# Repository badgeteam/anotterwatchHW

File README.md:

# AnOtter_Watch

ESP32 driven smart watch with 14-Bit, 2 MSPS Dual Channel scope and component tester.

[Schematics](/schematics_V1.1/anotterwatch.pdf) read more on the [Wiki](https://wiki.badge.team/AnOtter_Watch)

Designed in KiCad

## Current project status

Prototype d0a3733 ordered

[Gerber files](/gerber_V1.0.zip)

## V1.1

# Errors

 - [ ] ESP-Pico-D4 foorpint
 - [ ] Display cutout
 - [ ] TCA9535 GND level is ~0.5V when USB is unplugged
 - [ ] WS2812 leds are not working when USB is plugged
 - [ ] Button down can only be pressed when the battery is connected
 
# Tested
  
  - PMIC
  - Charging
  - WS2812
  - Display
  - I2C switch
  - USB-Plug
  - CH341C
  - Button

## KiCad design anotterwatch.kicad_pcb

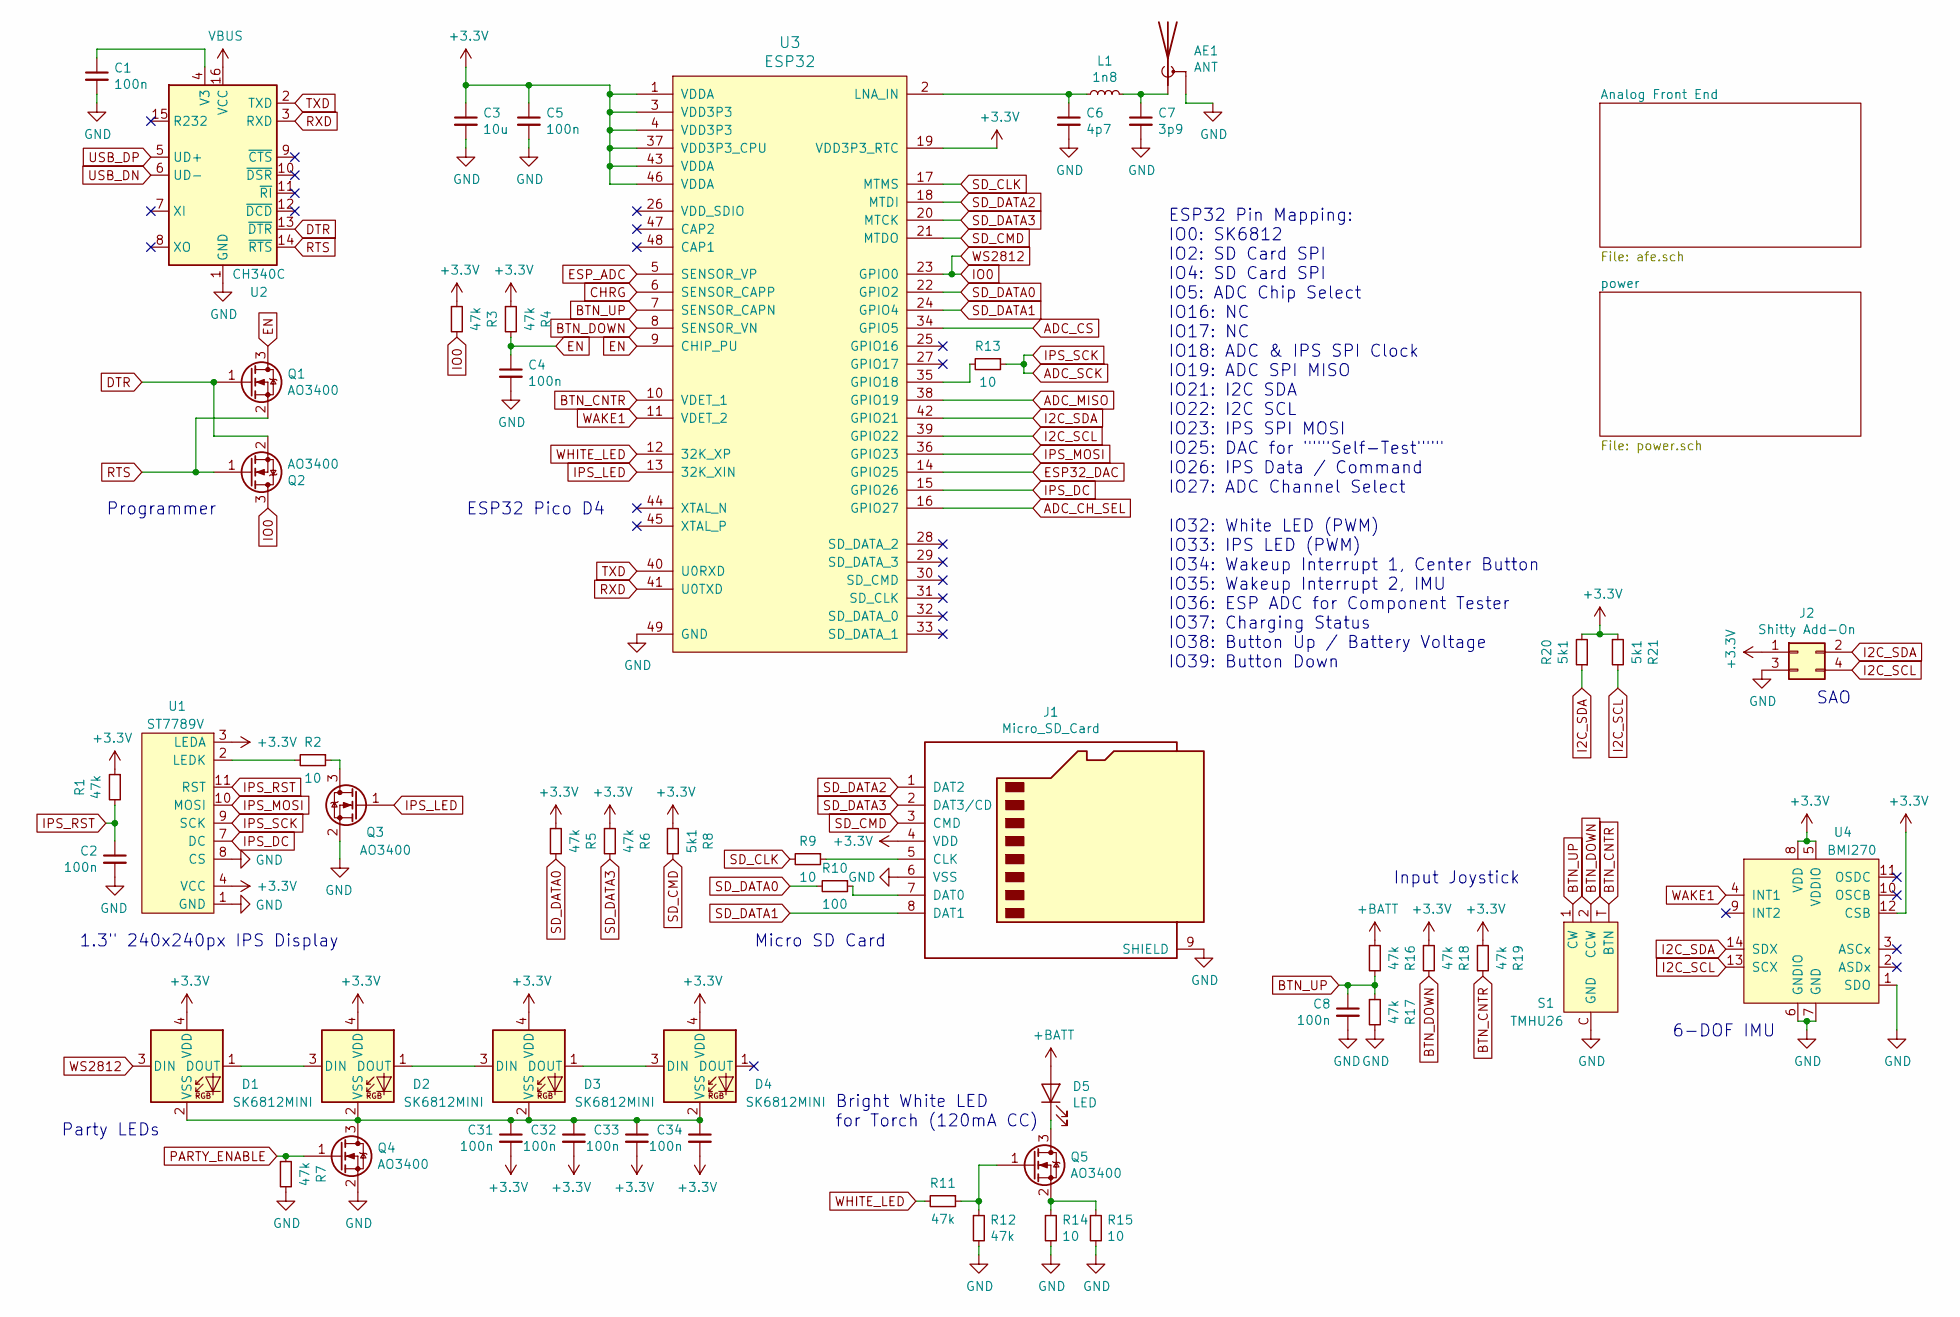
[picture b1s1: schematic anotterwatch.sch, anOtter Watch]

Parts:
AE1: ANT; Texas_SWRA117D_2.4GHz_Left
C1, C2, C4, C5, C8, C31, C32, C33, C34: 100n; C_0402_1005Metric
C3: 10u; C_0603_1608Metric
C6: 4p7; C_0402_1005Metric
C7: 3p9; C_0402_1005Metric
D1, D2, D3, D4: SK6812MINI; LED_SK6812MINI_PLCC4_3.5x3.5mm_P1.75mm
D5: LED; RZX-S020CCW-0.4T
J1: Micro_SD_Card; SUNTECH_ST-TF-003A
J2: Shitty Add-On; PinSocket_2x02_P2.54mm_Vertical_SMD
L1: 1n8; L_0603_1608Metric
Q1, Q2, Q3, Q4, Q5: AO3400; SOT-23
R1, R3, R4, R5, R6, R7, R11, R12, R16, R17, R18, R19: 47k; R_0402_1005Metric
R2, R9, R13, R14, R15: 10; R_0603_1608Metric
R8, R20, R21: 5k1; R_0402_1005Metric
R10: 100; R_0402_1005Metric
S1: TMHU26
U1: ST7789V
U2: CH340C; SOIC-16_3.9x9.9mm_P1.27mm
U3: ESP32; QFN-48-1EP_7x7mm_P0.5mm_EP5.3x5.3mm
U4: BMI270

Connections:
+3V3: C3.1, C5.1, C31.2, C32.2, C33.2, C34.2, D1.4 (VDD), D2.4 (VDD), D3.4 (VDD), D4.4 (VDD), J1.4 (VDD), J2.1, R1.1, R3.1, R4.1, R5.1, R6.1, R8.1, R18.1, R19.1, R20.2, R21.1, U1.3 (LEDA), U1.4 (VCC), U3.1 (VDDA), U3.3 (VDD3P3), U3.4 (VDD3P3), U3.19 (VDD3P3_RTC), U3.37 (VDD3P3_CPU), U3.43 (VDDA), U3.46 (VDDA), U4.5 (VDDIO), U4.8 (VDD), U4.12 (CSB); also elsewhere on the board
ADC_CH_SEL: U3.16 (GPIO27); also elsewhere on the board
ADC_CS: U3.34 (GPIO5); also elsewhere on the board
ADC_MISO: U3.38 (GPIO19); also elsewhere on the board
ADC_SCK: R13.1, U1.9 (SCK); also elsewhere on the board
BTN_CNTR: R19.2, S1.T (BTN), U3.10 (VDET_1)
BTN_DOWN: R18.2, S1.2 (CCW), U3.8 (SENSOR_VN)
BTN_UP: C8.1, R16.2, R17.1, S1.1 (CW), U3.7 (SENSOR_CAPN)
CHRG: U3.6 (SENSOR_CAPP); also elsewhere on the board
DTR: Q1.1 (G), Q2.2 (S), U2.13 (~DTR)
EN: C4.1, Q1.3 (D), R4.2, U3.9 (CHIP_PU)
ESP32_DAC: U3.14 (GPIO25); also elsewhere on the board
ESP_ADC: U3.5 (SENSOR_VP); also elsewhere on the board
GND: AE1.2 (Shield), C1.2, C2.2, C3.2, C4.2, C5.2, C6.2, C7.2, C8.2, J1.6 (VSS), J1.9 (SHIELD), J2.3, Q3.2 (S), Q4.2 (S), R7.2, R12.2, R14.2, R15.2, R17.2, S1.C (GND), U1.1 (GND), U1.5 (GND), U1.6 (GND), U1.8 (CS), U1.12, U2.1 (GND), U3.49 (GND), U4.1 (SDO), U4.6 (GNDIO), U4.7 (GND); also elsewhere on the board
I2C_SCL: J2.4, R21.2, U3.39 (GPIO22), U4.13 (SCX); also elsewhere on the board
I2C_SDA: J2.2, R20.1, U3.42 (GPIO21), U4.14 (SDX); also elsewhere on the board
IO0: D1.3 (DIN), Q2.3 (D), R3.2, U3.23 (GPIO0)
IPS_DC: U1.7 (DC), U3.15 (GPIO26)
IPS_LED: Q3.1 (G), U3.13 (32K_XIN)
IPS_MOSI: U1.10 (MOSI), U3.36 (GPIO23)
IPS_RST: C2.1, R1.2, U1.11 (RST)
unnamed: AE1.1 (A), C7.1, L1.2
unnamed: C1.1, U2.4 (V3)
unnamed: C6.1, L1.1, U3.2 (LNA_IN)
unnamed: C31.1, C32.1, C33.1, C34.1, D1.2 (VSS), D2.2 (VSS), D3.2 (VSS), D4.2 (VSS), Q4.3 (D)
unnamed: D1.1 (DOUT), D2.3 (DIN)
unnamed: D2.1 (DOUT), D3.3 (DIN)
unnamed: D3.1 (DOUT), D4.3 (DIN)
unnamed: J1.5 (CLK), R9.1
unnamed: J1.7 (DAT0), R10.1
unnamed: Q3.3 (D), R2.1
unnamed: Q5.1 (G), R11.1, R12.1
unnamed: Q5.2 (S), R14.1, R15.1
unnamed: R2.2, U1.2 (LEDK)
unnamed: R13.2, U3.35 (GPIO18)
PARTY_ENABLE: Q4.1 (G), R7.1; also elsewhere on the board
RTS: Q1.2 (S), Q2.1 (G), U2.14 (~RTS)
RXD: U2.3 (RXD), U3.41 (U0TXD)
SD_CLK: R9.2, U3.17 (MTMS)
SD_CMD: J1.3 (CMD), R8.2, U3.21 (MTDO)
SD_DATA0: R5.2, R10.2, U3.22 (GPIO2)
SD_DATA1: J1.8 (DAT1), U3.24 (GPIO4)
SD_DATA2: J1.1 (DAT2), U3.18 (MTDI)
SD_DATA3: J1.2 (DAT3/CD), R6.2, U3.20 (MTCK)
TXD: U2.2 (TXD), U3.40 (U0RXD)
USB_DN: U2.6 (UD-); also elsewhere on the board
USB_DP: U2.5 (UD+); also elsewhere on the board
VBUS: U2.16 (VCC); also elsewhere on the board
WAKE1: U3.11 (VDET_2), U4.4 (INT1)
WHITE_LED: R11.2, U3.12 (32K_XP)

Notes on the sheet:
ESP32 Pin Mapping: IO0: SK6812 IO2: SD Card SPI IO4: SD Card SPI IO5: ADC Chip Select IO16: NC IO17: NC IO18: ADC & IPS SPI Clock IO19: ADC SPI MISO IO21: I2C SDA IO22: I2C SCL IO23: IPS SPI MOSI IO25: DAC for """Self-Test""" IO26: IPS Data / Command IO27: ADC Channel Select IO32: White LED (PWM) I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
Programmer
1.3" 240x240px IPS Display
Party LEDs
Bright White LED for Torch (120mA CC)
Micro SD Card
Input Joystick
6-DOF IMU
SAO
ESP32 Pico D4

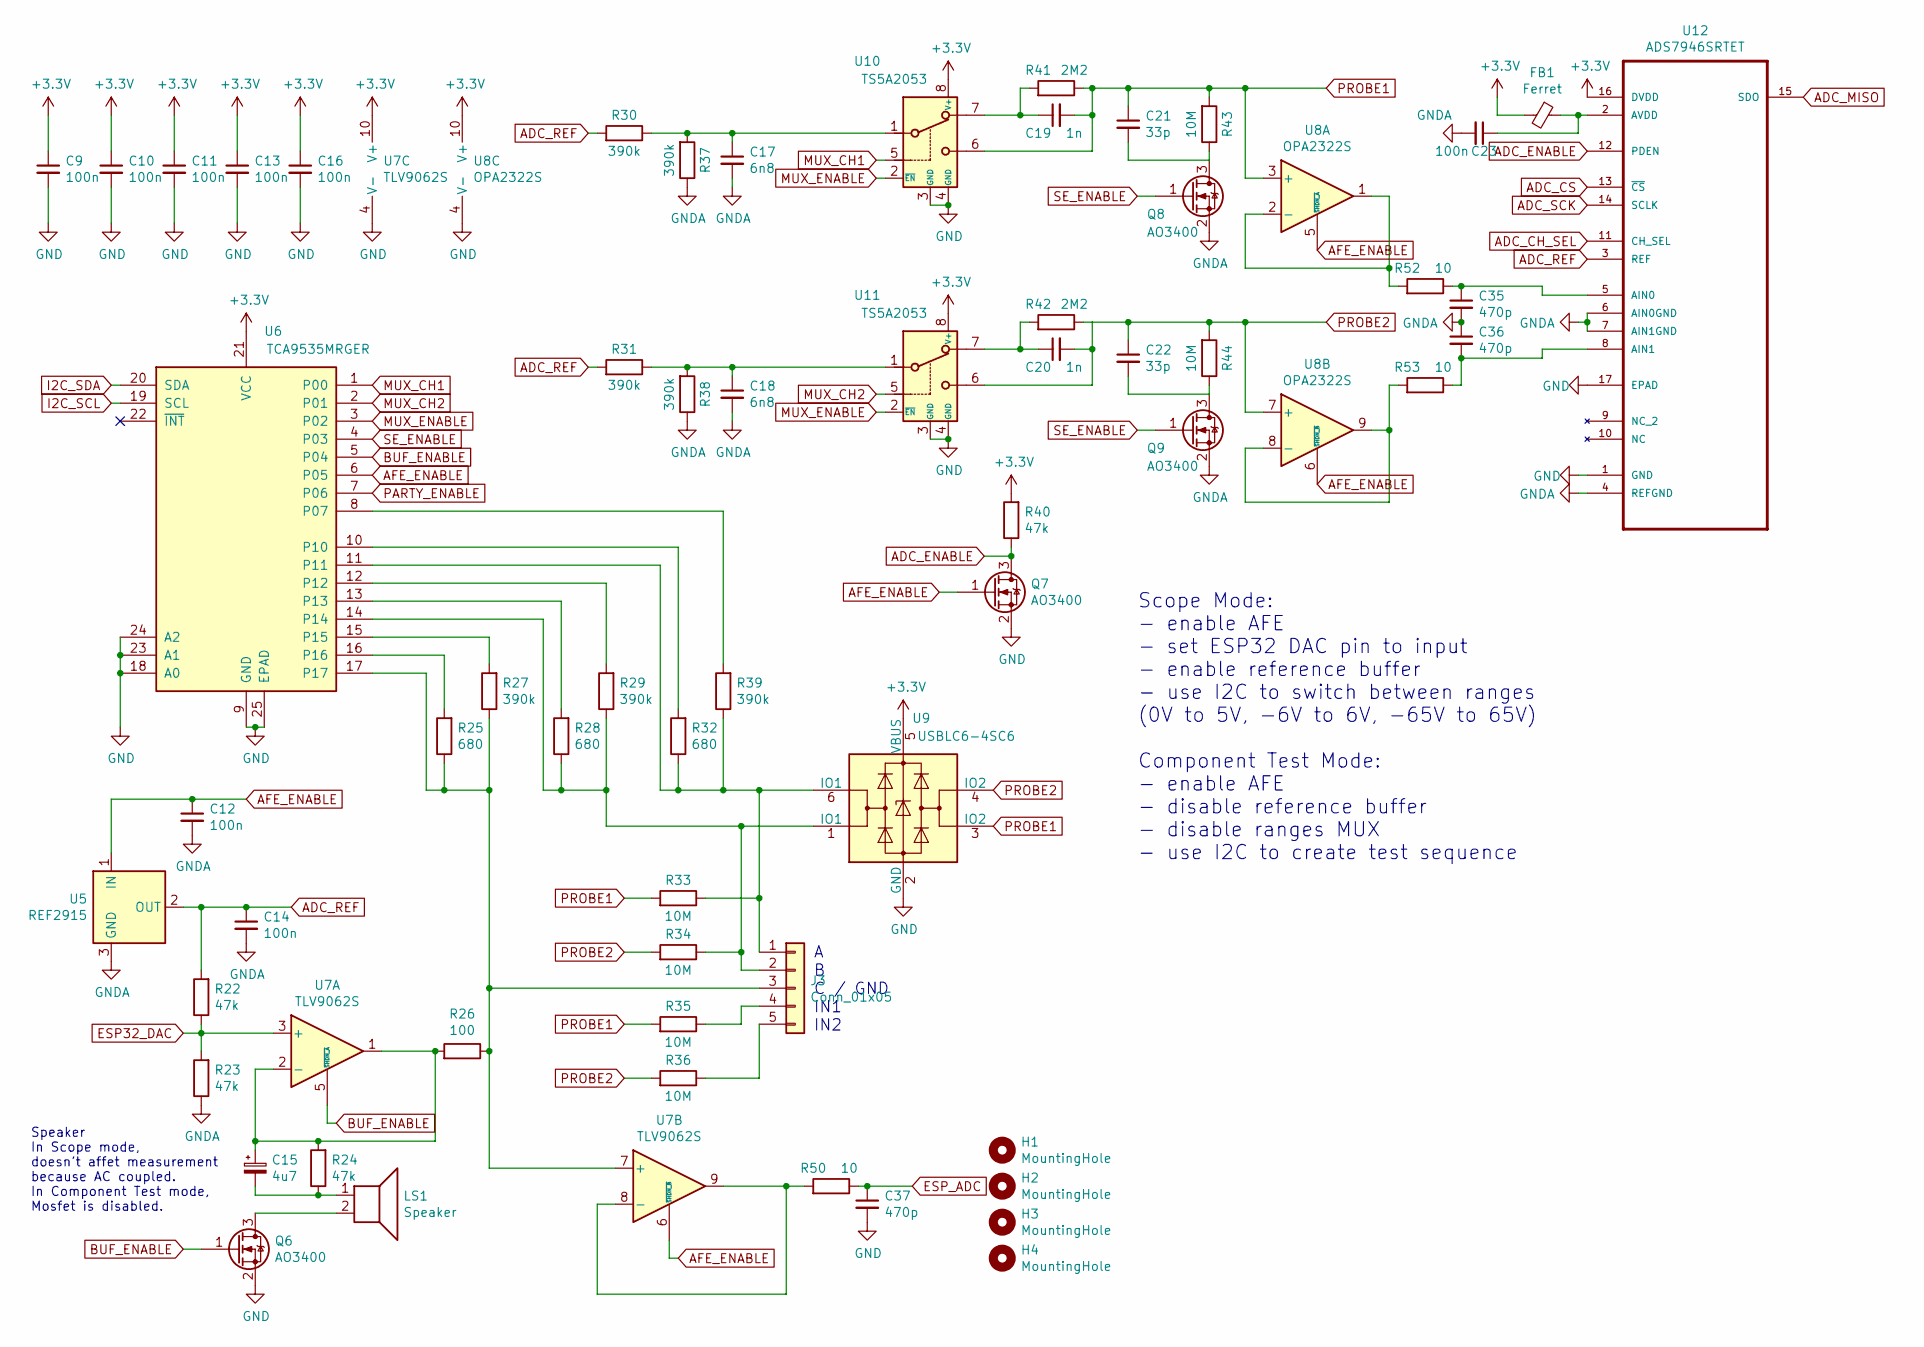
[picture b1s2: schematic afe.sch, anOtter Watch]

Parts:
C9, C10, C11, C12, C13, C14, C16: 100n; C_0402_1005Metric
C15: 4u7; C_0603_1608Metric
C17, C18: 6n8; C_0402_1005Metric
C19, C20: 1n; C_0402_1005Metric
C21, C22: 33p; C_0402_1005Metric
C23: 100n; C_0603_1608Metric
C35, C36, C37: 470p; C_0402_1005Metric
FB1: Ferret; L_0603_1608Metric
H1, H2, H3, H4: MountingHole; MountingHole_2.2mm_M2
J3: Conn_01x05; PinHeader_1x05_P2.54mm_Vertical_SMD_Pin1Left
LS1: Speaker; Molex_KK-254_AE-6410-02A_1x02_P2.54mm_Vertical
Q6, Q7, Q8, Q9: AO3400; SOT-23
R22, R23, R24, R40: 47k; R_0402_1005Metric
R25, R28, R32: 680; R_0402_1005Metric
R26: 100; R_0402_1005Metric
R27, R29, R30, R31, R37, R38, R39: 390k; R_0402_1005Metric
R33, R34, R35, R36: 10M; R_0603_1608Metric
R41, R42: 2M2; R_0402_1005Metric
R43, R44: 10M; R_0402_1005Metric
R50, R52, R53: 10; R_0603_1608Metric
U5: REF2915; SOT-23
U6: TCA9535MRGER; QFN-24-1EP_4x4mm_P0.5mm_EP2.6x2.6mm
U7: TLV9062S; VSSOP-10
U8: OPA2322S; VSSOP-10
U9: USBLC6-4SC6; SOT-23-6
U10, U11: TS5A2053; VSSOP-8_2.4x2.1mm_P0.5mm
U12: ADS7946SRTET; QFN-16-1EP_3x3mm_P0.5mm_EP1.8x1.8mm

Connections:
+3V3: C9.1, C10.1, C11.1, C13.1, C16.1, FB1.2, R40.2, U6.21 (VCC), U7.10 (V+), U8.10 (V+), U9.5 (VBUS), U10.8 (V+), U11.8 (V+), U12.16 (DVDD); also elsewhere on the board
ADC_CH_SEL: U12.11 (CH_SEL); also elsewhere on the board
ADC_CS: U12.13 (~CS~); also elsewhere on the board
ADC_ENABLE: Q7.3 (D), R40.1, U12.12 (PDEN)
ADC_MISO: U12.15 (SDO); also elsewhere on the board
ADC_REF: C14.1, R22.2, R30.2, R31.2, U5.2 (OUT), U12.3 (REF)
ADC_SCK: U12.14 (SCLK); also elsewhere on the board
AFE_ENABLE: C12.1, Q7.1 (G), U5.1 (IN), U6.6 (P05), U7.6 (~SHDN_B), U8.5 (~SHDN_A), U8.6 (~SHDN_B)
BUF_ENABLE: Q6.1 (G), U6.5 (P04), U7.5 (~SHDN_A)
ESP32_DAC: R22.1, R23.2, U7.3 (+); also elsewhere on the board
ESP_ADC: C37.1, R50.1; also elsewhere on the board
GND: C9.2, C10.2, C11.2, C13.2, C16.2, C37.2, Q6.2 (S), Q7.2 (S), U6.9 (GND), U6.18 (A0), U6.23 (A1), U6.24 (A2), U6.25 (EPAD), U7.4 (V-), U7.11 (V-), U8.4 (V-), U8.11 (V-), U9.2 (GND), U10.3 (GND), U10.4 (GND), U11.3 (GND), U11.4 (GND), U12.1 (GND), U12.17 (EPAD); also elsewhere on the board
GNDA: C12.2, C14.2, C17.2, C18.2, C23.2, C35.2, C36.1, Q8.2 (S), Q9.2 (S), R23.1, R37.1, R38.1, U5.3 (GND), U12.4 (REFGND), U12.6 (AIN0GND), U12.7 (AIN1GND)
I2C_SCL: U6.19 (SCL); also elsewhere on the board
I2C_SDA: U6.20 (SDA); also elsewhere on the board
MUX_CH1: U6.1 (P00), U10.5
MUX_CH2: U6.2 (P01), U11.5
MUX_ENABLE: U6.3 (P02), U10.2 (~EN), U11.2 (~EN)
unnamed: C15.1, R24.2, R26.2, U7.1, U7.2 (-)
unnamed: C15.2, LS1.1, R24.1
unnamed: C17.1, R30.1, R37.2, U10.1
unnamed: C18.1, R31.1, R38.2, U11.1
unnamed: C19.1, R41.2, U10.7
unnamed: C20.1, R42.2, U11.7
unnamed: C21.2, Q8.3 (D), R43.1
unnamed: C22.2, Q9.3 (D), R44.1
unnamed: C23.1, FB1.1, U12.2 (AVDD)
unnamed: C35.1, R52.1, U12.5 (AIN0)
unnamed: C36.2, R53.1, U12.8 (AIN1)
unnamed: J3.1, R32.1, R33.1, R39.1, U6.11, U9.6 (IO1)
unnamed: J3.2, R28.1, R29.1, R34.1, U6.14, U9.1 (IO1)
unnamed: J3.3, R25.1, R26.1, R27.1, U6.17, U7.7 (+)
unnamed: J3.4, R35.1
unnamed: J3.5, R36.1
unnamed: LS1.2, Q6.3 (D)
unnamed: R25.2, U6.16
unnamed: R27.2, U6.15
unnamed: R28.2, U6.13
unnamed: R29.2, U6.12
unnamed: R32.2, U6.10
unnamed: R39.2, U6.8 (P07)
unnamed: R50.2, U7.8 (-), U7.9
unnamed: R52.2, U8.1, U8.2 (-)
unnamed: R53.2, U8.8 (-), U8.9
PARTY_ENABLE: U6.7 (P06); also elsewhere on the board
PROBE1: C19.2, C21.1, R33.2, R35.2, R41.1, R43.2, U8.3 (+), U9.3 (IO2), U10.6
PROBE2: C20.2, C22.1, R34.2, R36.2, R42.1, R44.2, U8.7 (+), U9.4 (IO2), U11.6
SE_ENABLE: Q8.1 (G), Q9.1 (G), U6.4 (P03)

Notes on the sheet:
A B C / GND IN1 IN2
Scope Mode: - enable AFE - set ESP32 DAC pin to input - enable reference buffer - use I2C to switch between ranges (0V to 5V, -6V to 6V, -65V to 65V) Component Test Mode: - enable AFE - disable reference buffer - disable ranges MUX - use I2C to create test sequence
Speaker In Scope mode, doesn't affet measurement because AC coupled. In Component Test mode, Mosfet is disabled.

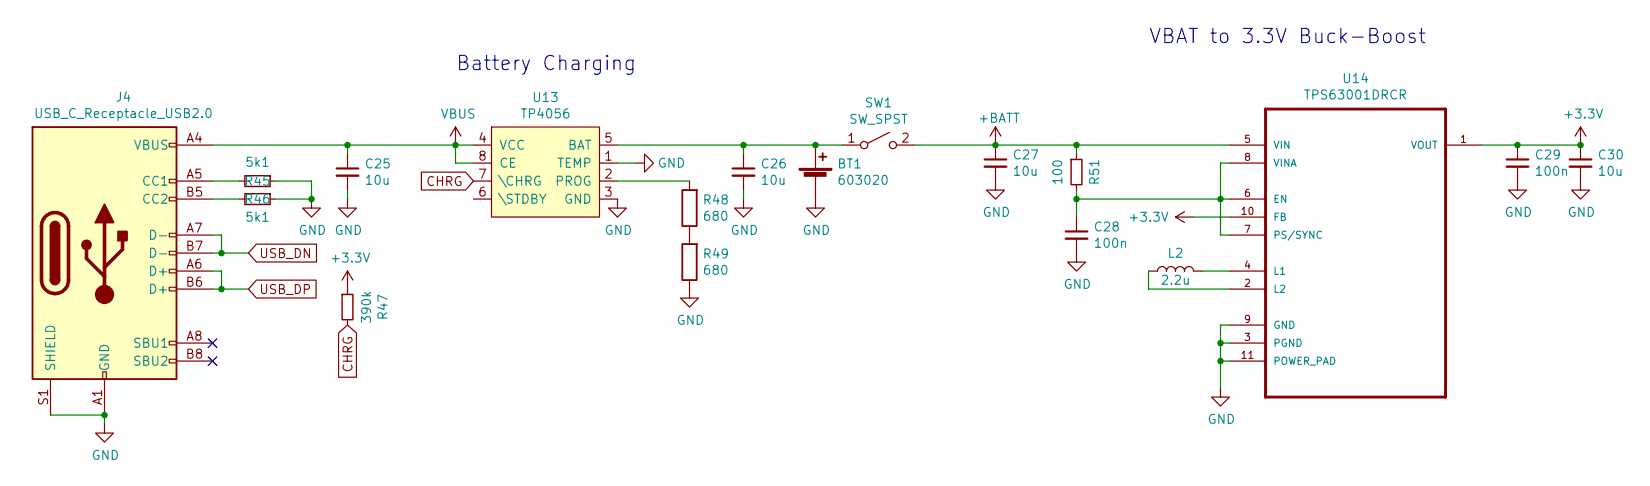
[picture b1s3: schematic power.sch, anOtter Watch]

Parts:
BT1: 603020; JST_GH_BM02B-GHS-TBT_1x02-1MP_P1.25mm_Vertical
C25, C26, C27, C30: 10u; C_0603_1608Metric
C28, C29: 100n; C_0402_1005Metric
J4: USB_C_Receptacle_USB2.0; USB-C 16Pin
L2: 2.2u; L_Taiyo-Yuden_MD-3030
R45, R46: 5k1; R_0402_1005Metric
R47: 390k; R_0402_1005Metric
R48, R49: 680; R_0402_1005Metric
R51: 100; R_0402_1005Metric
SW1: SW_SPST; SW_SPDT_PCM12
U13: TP4056; Diodes_PSOP-8
U14: TPS63001DRCR; Texas_S-PVSON-N10

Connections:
+3V3: C29.1, C30.1, R47.1, U14.1 (VOUT), U14.10 (FB); also elsewhere on the board
CHRG: R47.2, U13.7 (\CHRG); also elsewhere on the board
GND: BT1.2 (-), C25.2, C26.2, C27.2, C28.2, C29.2, C30.2, J4.A1 (GND), J4.A12 (GND), J4.B1 (GND), J4.B12 (GND), J4.S1 (SHIELD), R45.1, R46.1, R49.1, U13.1 (TEMP), U13.3 (GND), U14.3 (PGND), U14.9 (GND), U14.11 (POWER_PAD); also elsewhere on the board
unnamed: BT1.1 (+), C26.1, SW1.1 (A), U13.5 (BAT)
unnamed: C28.1, R51.2, U14.6 (EN), U14.7 (PS/SYNC), U14.8 (VINA)
unnamed: J4.A5 (CC1), R45.2
unnamed: J4.B5 (CC2), R46.2
unnamed: L2.1, U14.2 (L2)
unnamed: L2.2, U14.4 (L1)
unnamed: R48.1, R49.2
unnamed: R48.2, U13.2 (PROG)
USB_DN: J4.A7 (D-), J4.B7 (D-); also elsewhere on the board
USB_DP: J4.A6 (D+), J4.B6 (D+); also elsewhere on the board
VBUS: C25.1, J4.A4 (VBUS), J4.A9 (VBUS), J4.B4 (VBUS), J4.B9 (VBUS), U13.4 (VCC), U13.8 (CE); also elsewhere on the board

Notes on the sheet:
VBAT to 3.3V Buck-Boost
Battery Charging

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
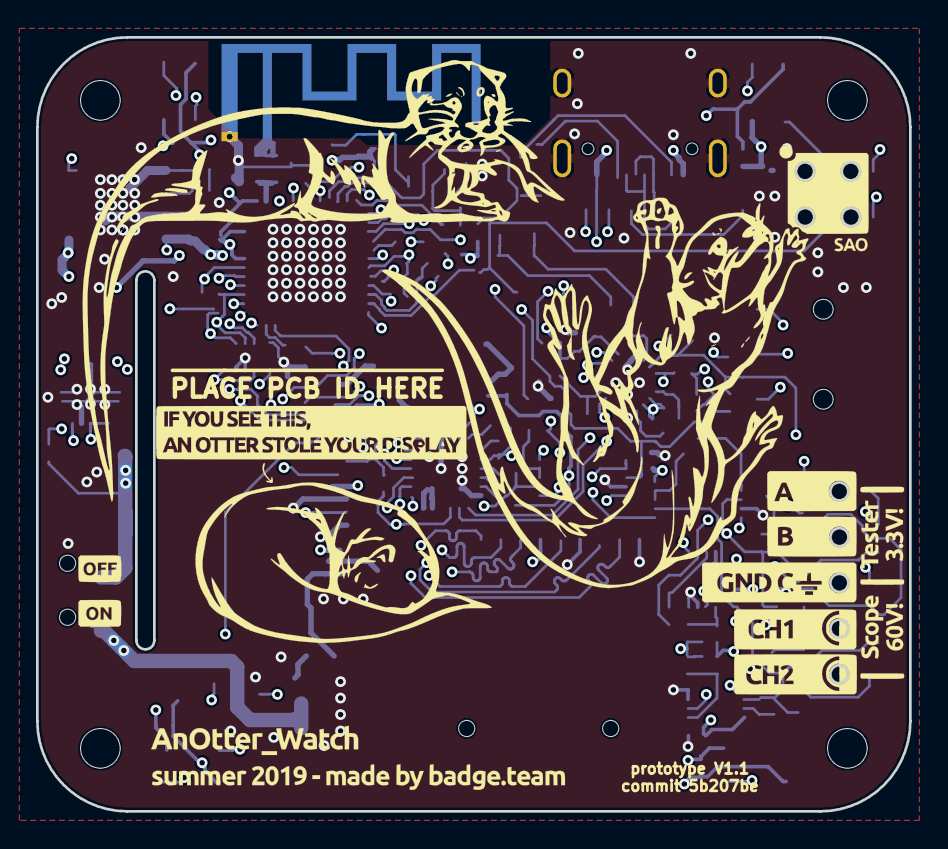
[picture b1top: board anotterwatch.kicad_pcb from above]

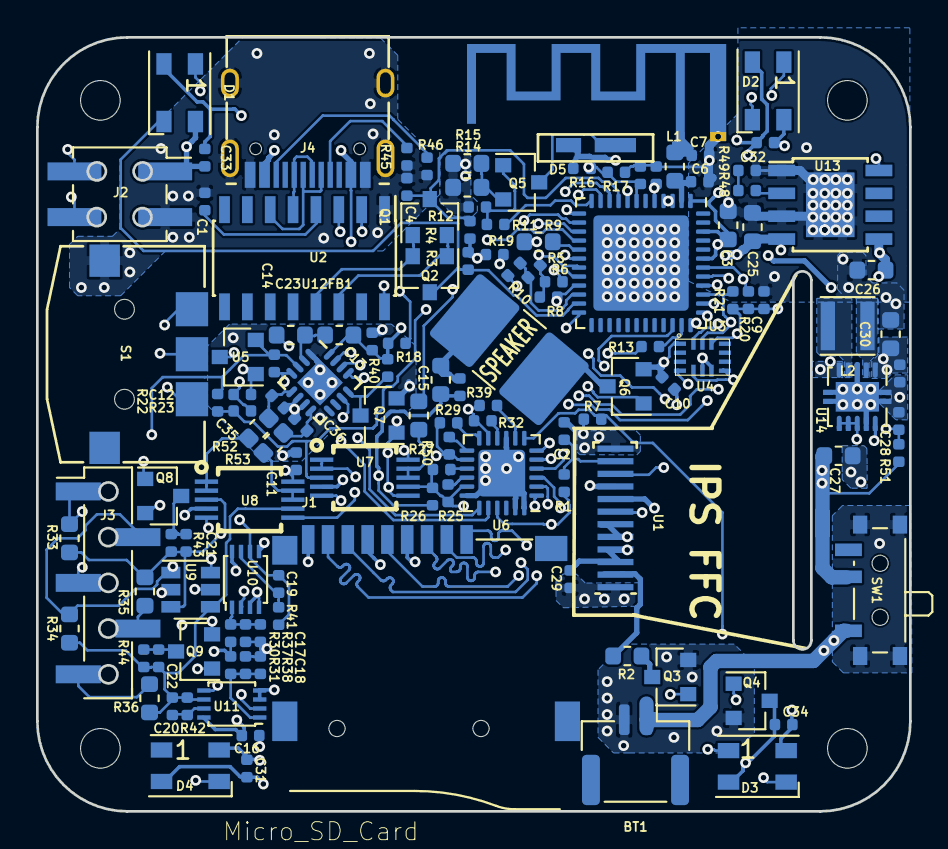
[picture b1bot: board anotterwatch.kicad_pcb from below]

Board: 4 copper layers, 48.5 x 43.0 mm, 132 parts (128 on the bottom side), 97 nets.

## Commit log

2019-02-20 added gitignore
2019-02-20 initial commit #2
2019-02-20 added USB-C connector
2019-02-20 created USB-C connector footprint
2019-02-20 added sk6812
2019-02-20 added led
2019-02-20 added led footprint
2019-02-20 added datasheets
2019-02-22 added displays footprint
2019-02-22 fixed lib
2019-02-22 added display + datasheet, removed VDD added VCC
2019-02-22 moved LED A and K
2019-02-22 added display footprint
2019-02-23 added reset circuit
2019-02-23 added esp
2019-02-23 added datasheet esp
2019-02-24 fixed display lib
2019-02-24 Im an Otter
2019-02-24 Im an Otter #2
2019-02-24 ADD: Analog Front-End
2019-02-24 added switch
2019-02-24 ADD: Jog switch
2019-02-24 updated display foorpint
2019-02-24 added switch symbol
2019-02-25 added tp4056
2019-02-25 ADD: ESP32 pinout
2019-02-25 added BMI270
2019-02-25 added BMI and TPS
2019-02-25 added TPS lib
2019-02-25 *white smoke*
2019-02-25 ADD: speaker
2019-02-25 ADD: speaker fet to make it compagtible to component tester mode
2019-02-26 added power schematics
2019-02-26 Schematic cleanup
2019-02-26 added power sheet
2019-02-26 updated pdf
2019-02-26 added datasheets and descriptions
2019-02-26 renamed power.sch
2019-02-26 add anotation
2019-02-26 added SD Card socket lib
2019-02-26 removed html file
2019-02-26 added SD Card socket footprint
2019-02-26 added VEML6075 to lib
2019-02-26 added shitty addon todo
2019-02-26 UPD: finalized schematic, started layout
2019-02-26 Finalized front
2019-02-28 ADD: constant current source for high power LED
2019-02-28 ADD:started to place footprints
2019-03-01 ADD: started routing
2019-03-01 ADD: tbc
2019-03-01 fixed display footprint
2019-03-01 fixed TMHU symbol
2019-03-01 fixed USB-C pinout
2019-03-01 fixed label and unconnected net
2019-03-01 added USB-C datasheet
2019-03-01 added pwoer layout
2019-03-01 UPD: removed all p-fets, no more ideal diode
2019-03-01 fixed 3D models
2019-03-04 Finished layout
2019-03-04 Finished silkscreen
2019-03-04 Final design for first prototype
2019-03-05 ADD: finalized artwork, first pcbs ordered
2019-04-01 added esp32-pico-d4 footprint
2019-04-08 FIX: ESP32 new footprint, fix LED polarity, fix IPS FFC position
2019-04-08 V1.1 -> Production
